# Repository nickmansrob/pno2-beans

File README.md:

# The Bean Bot

As of 20th of May 2022, this project is discontinued and will no longer be maintained.

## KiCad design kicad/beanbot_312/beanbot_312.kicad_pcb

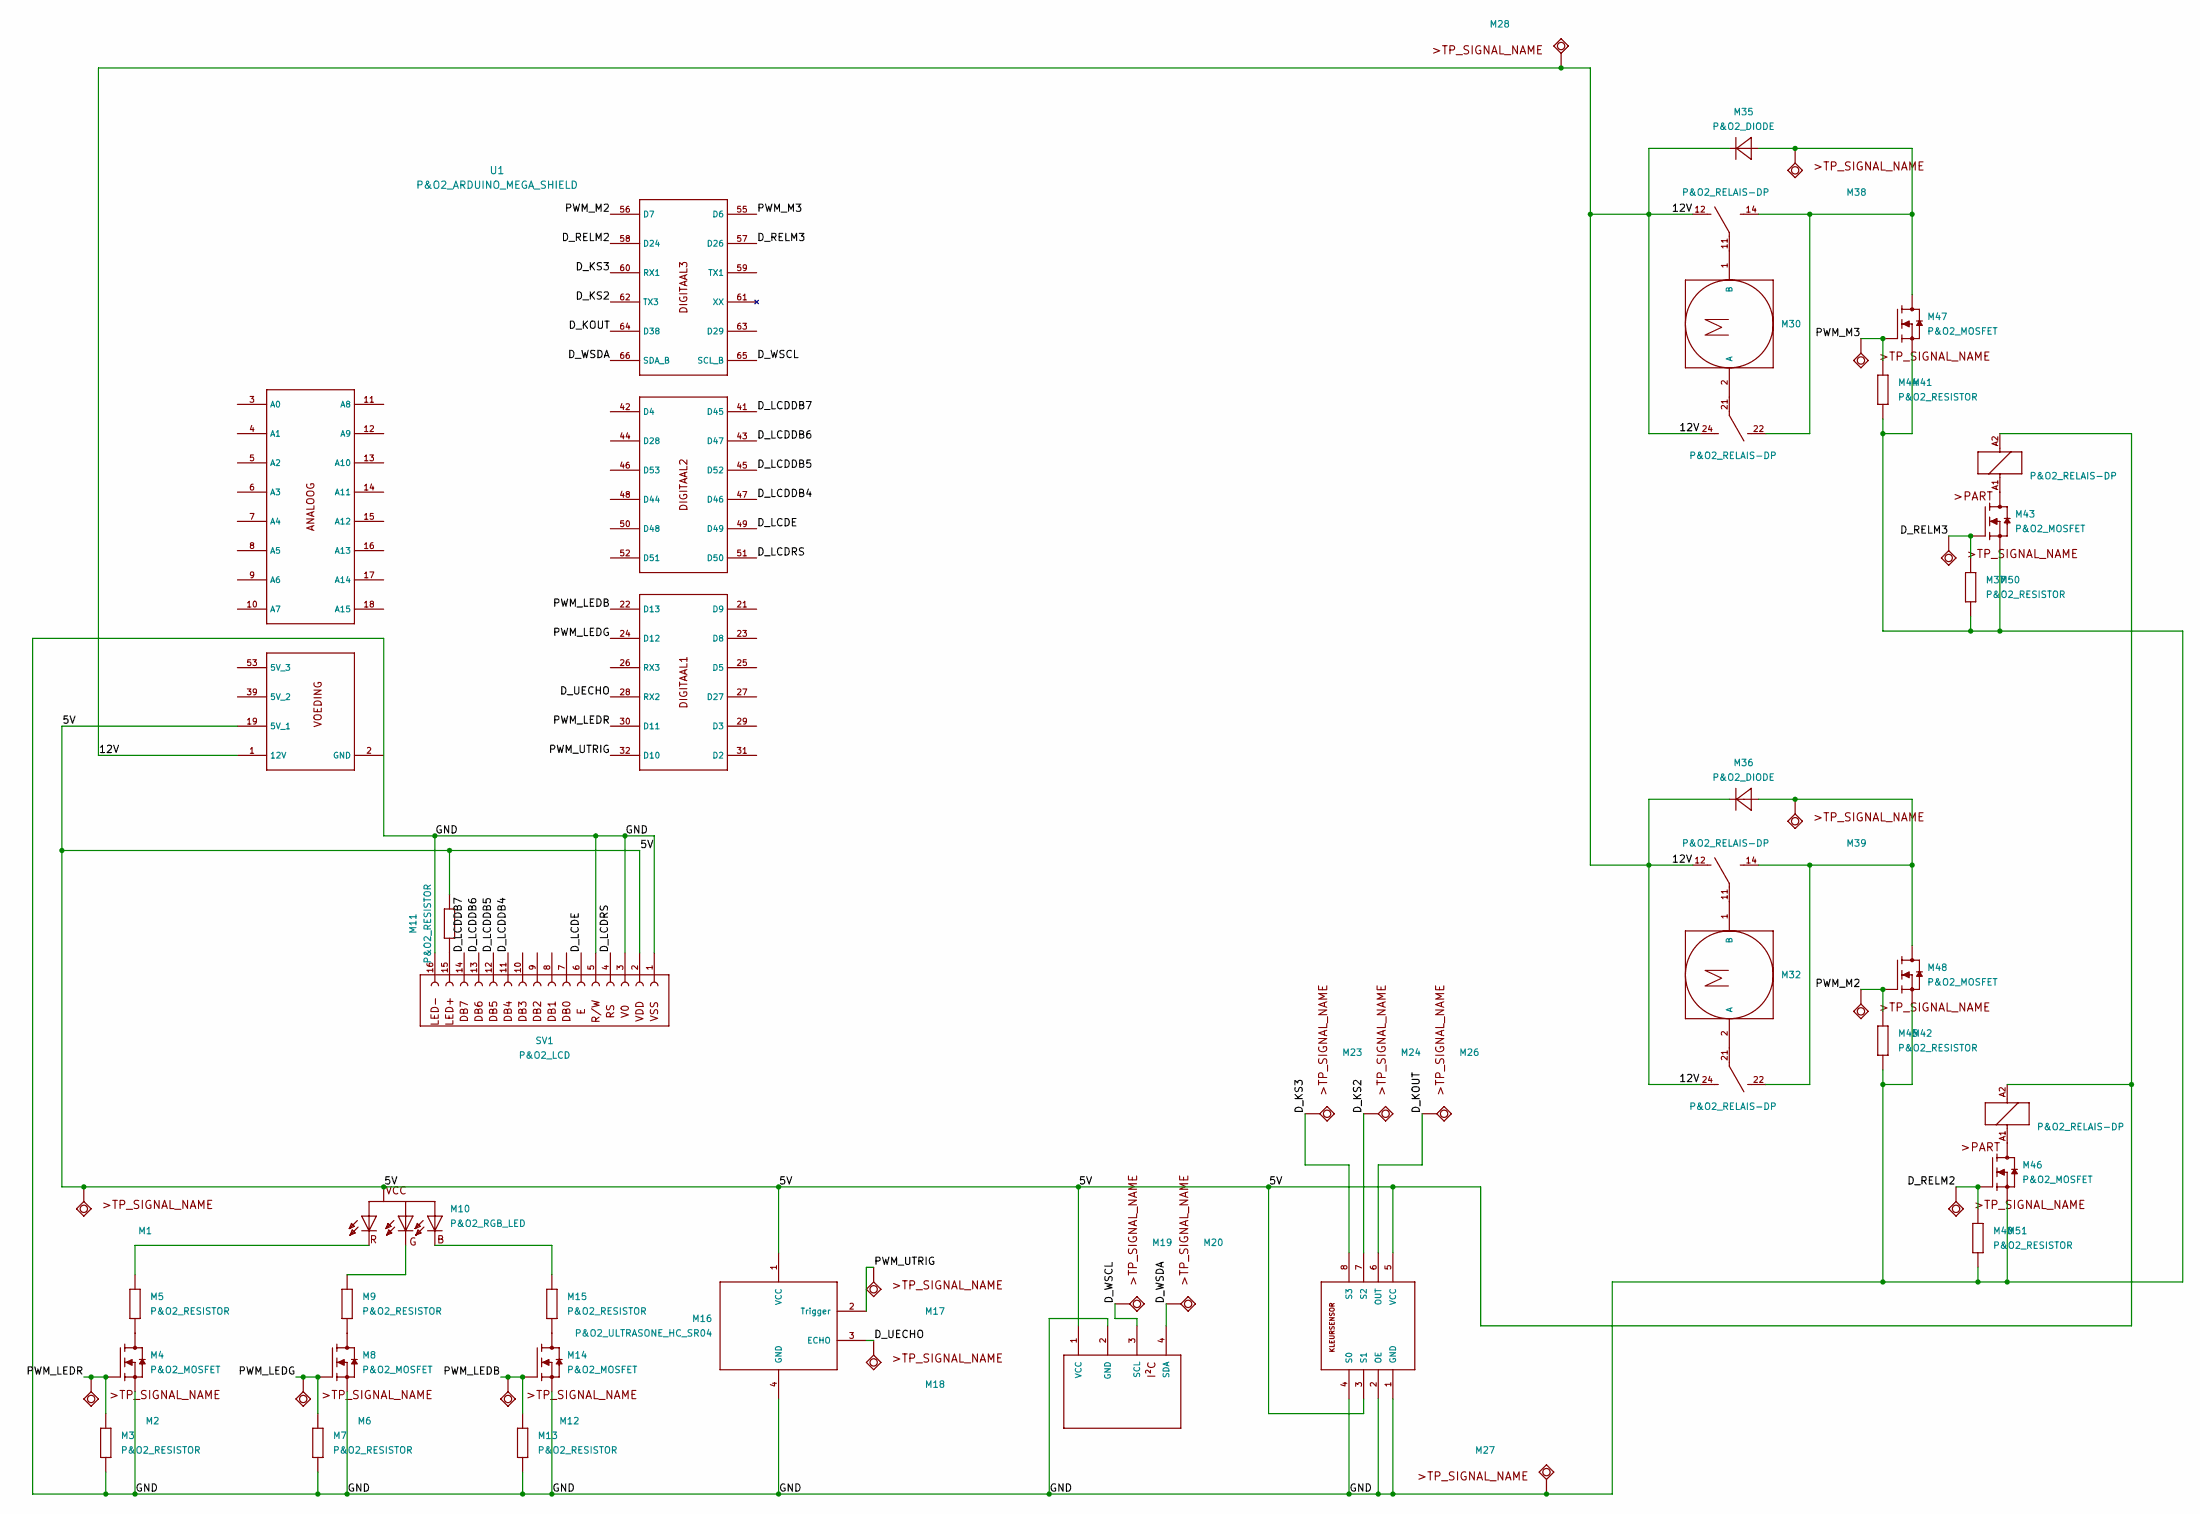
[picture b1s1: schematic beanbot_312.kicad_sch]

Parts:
M1, M2, M6, M12, M17, M18, M19, M20, M23, M24, M26, M27, M28, M38, M39, M41, M42, M50, M51: P&O2_MEETPUNT
M3, M5, M7, M9, M11, M13, M15, M37, M40, M44, M45: P&O2_RESISTOR
M4, M8, M14, M43, M46, M47, M48: P&O2_MOSFET; P&O2_TO220
M10: P&O2_RGB_LED
M16: P&O2_ULTRASONE_HC_SR04; P&O2_ULTRASONE
M21: P&O2_GEWICHTSENSOR2; P&O2_GEWICHTSENSOR-4PIN
M25: P&O2_KLEURSENSOR; P&O2_KLEURENSENSOR-8PIN
M29, M31: P&O2_RELAIS-DP; P&O2_RELAY-DP
M30, M32: P&O2_DC-MOTOR; P&O2_2PIN-SCREW-5.08
M35, M36: P&O2_DIODE
SV1: P&O2_LCD
U1: P&O2_ARDUINO_MEGA_SHIELD

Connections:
/5V: M1.1 (TP), M10.2 (VCC), M11.2, M16.1 (VCC), M21.1 (VCC), M25.3 (S1), M25.5 (VCC), M29.A2 (2), M31.A2 (2), SV1.2, U1.19 (5V_1), U1.39 (5V_2), U1.53 (5V_3)
/12V: M28.1 (TP), M29.12 (1), M29.24 (1), M31.12 (1), M31.24 (1), M35.C, M36.C, U1.1 (12V)
/D_KOUT: M25.6 (OUT), M26.1 (TP), U1.64 (D38)
/D_KS2: M24.1 (TP), M25.7 (S2), U1.62 (TX3)
/D_KS3: M23.1 (TP), M25.8 (S3), U1.60 (RX1)
/D_LCDDB4: SV1.11, U1.47 (D46)
/D_LCDDB5: SV1.12, U1.45 (D52)
/D_LCDDB6: SV1.13, U1.43 (D47)
/D_LCDDB7: SV1.14, U1.41 (D45)
/D_LCDE: SV1.6, U1.49 (D49)
/D_LCDRS: SV1.4, U1.51 (D50)
/D_RELM2: M40.1, M46.1 (eG), M51.1 (TP), U1.58 (D24)
/D_RELM3: M37.1, M43.1 (eG), M50.1 (TP), U1.57 (D26)
/D_UECHO: M16.3 (ECHO), M18.1 (TP), U1.28 (RX2)
/D_WSCL: M19.1 (TP), M21.3 (SCL), U1.65 (SCL_B)
/D_WSDA: M20.1 (TP), M21.4 (SDA), U1.66 (SDA_B)
/GND: M3.2, M4.3 (S), M7.2, M8.3 (S), M13.2, M14.3 (S), M16.4 (GND), M21.2 (GND), M25.1 (GND), M25.2 (OE), M25.4 (S0), M27.1 (TP), M37.2, M40.2, M43.3 (S), M44.2, M45.2, M46.3 (S), M47.3 (S), M48.3 (S), SV1.1, SV1.3, SV1.5, SV1.16, U1.2 (GND)
/PWM_LEDB: M12.1 (TP), M13.1, M14.1 (eG), U1.22 (D13)
/PWM_LEDG: M6.1 (TP), M7.1, M8.1 (eG), U1.24 (D12)
/PWM_LEDR: M2.1 (TP), M3.1, M4.1 (eG), U1.30 (D11)
/PWM_M2: M42.1 (TP), M45.1, M48.1 (eG), U1.56 (D7)
/PWM_M3: M41.1 (TP), M44.1, M47.1 (eG), U1.55 (D6)
/PWM_UTRIG: M16.2 (Trigger), M17.1 (TP), U1.32 (D10)
unnamed: M4.2 (D), M5.2
unnamed: M8.2 (D), M9.2
unnamed: M5.1, M10.1 (R)
unnamed: M9.1, M10.3 (G)
unnamed: M10.4 (B), M15.1
unnamed: M11.1, SV1.15
unnamed: M14.2 (D), M15.2
unnamed: M29.11 (1), M30.1 (B)
unnamed: M29.14 (1), M29.22 (1), M35.A, M38.1 (TP), M47.2 (D)
unnamed: M29.21 (1), M30.2 (A)
unnamed: M29.A1 (1), M43.2 (D)
unnamed: M31.11 (1), M32.1 (B)
unnamed: M31.14 (1), M31.22 (1), M36.A, M39.1 (TP), M48.2 (D)
unnamed: M31.21 (1), M32.2 (A)
unnamed: M31.A1 (1), M46.2 (D)

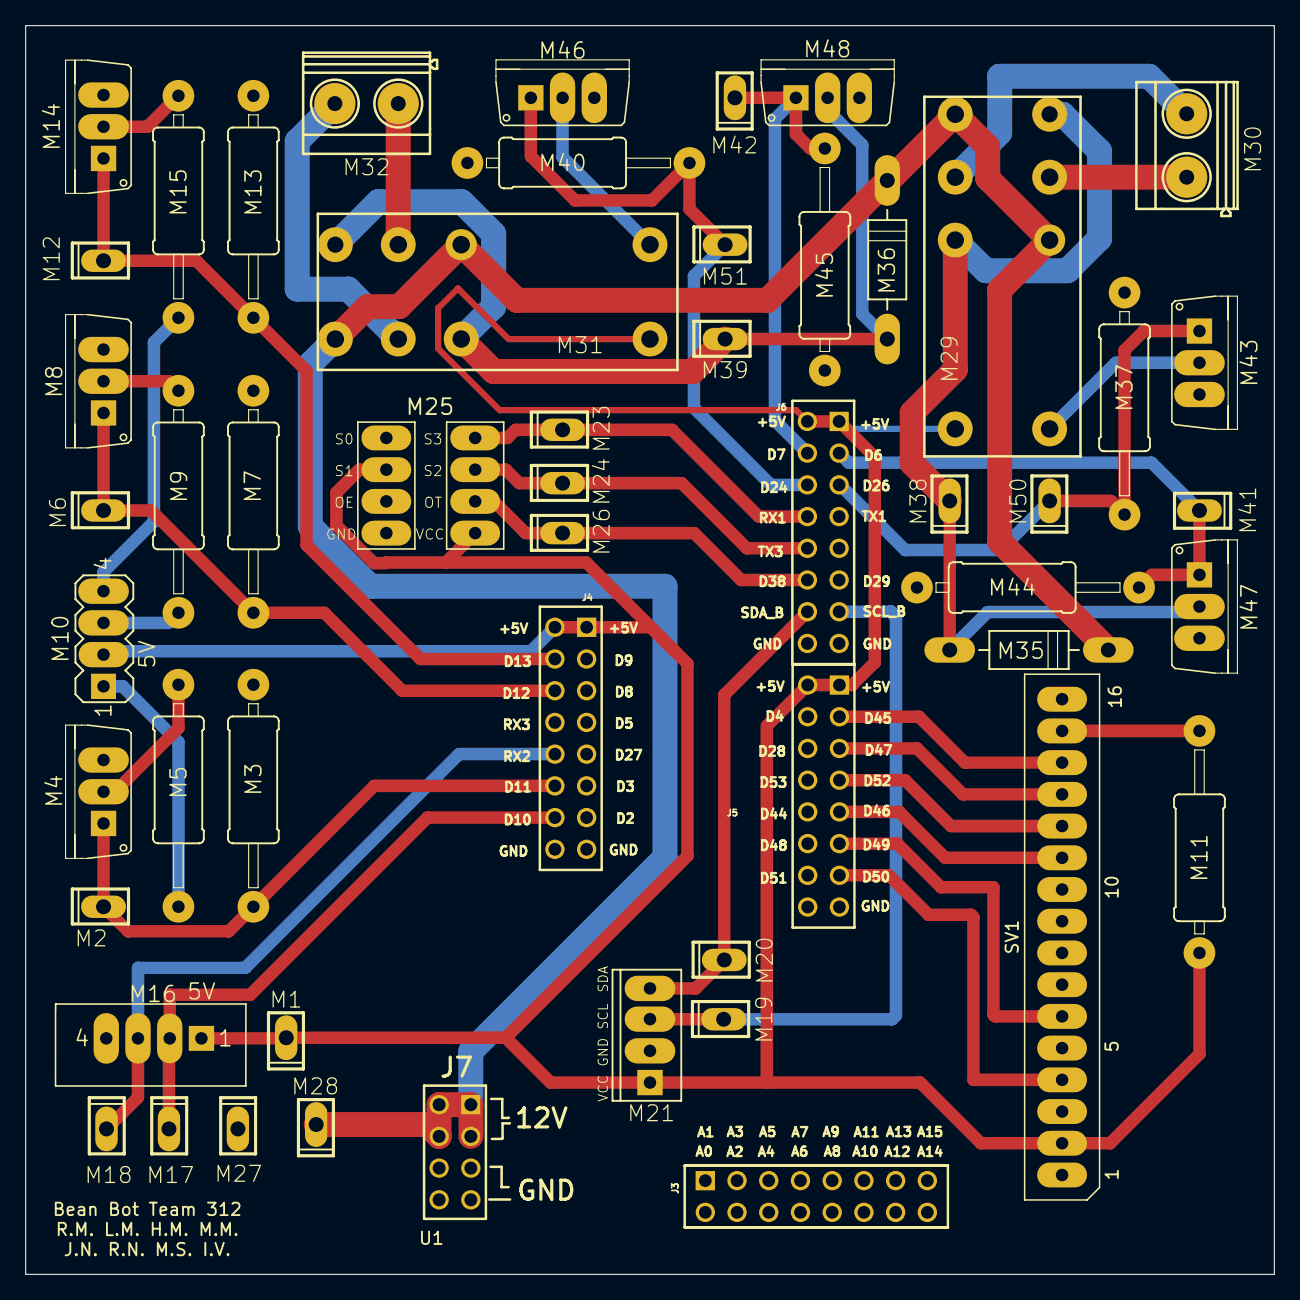
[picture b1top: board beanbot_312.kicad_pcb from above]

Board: 2 copper layers, 100.0 x 100.0 mm, 49 parts (0 on the bottom side), 38 nets.

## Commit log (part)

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2022-02-18 Initialized Flutter
2022-02-26 Created initial UI
2022-02-26 added arduino code
2022-02-26 moved readme
2022-02-26 Added navigation with PopupMenu
2022-02-27 Progress to logs page
2022-02-27 Some Progress on Debug Menu
    I created a Debug page like you created in the PDF document. It was not yet possible to properly implement the output containers due to problems with the heigth.
2022-02-27 Grouped items in debug.dart
2022-02-27 Force fix
2022-02-27 Update README (#1)
2022-03-03 Add ShowWeigth
2022-03-03 Added manual override
2022-03-03 established connection
2022-03-03 finished publishing
2022-03-03 added change ip button
2022-03-04 Commit changes
2022-03-04 added mqtt connection
2022-03-05 implemented handlers
2022-03-05 cleanup
2022-03-06 fixed pointer issue
2022-03-06 added kicad drawings
2022-03-06 added arduino compat
2022-03-06 Added Ip button
2022-03-07 Arduino/add mqtt (#5)
    * established connection
    * finished publishing
    * added change ip button
    * added mqtt connection
    * implemented handlers
    * cleanup
2022-03-08 Progress on KiCad drawings
2022-03-08 Some progress on the home page
2022-03-08 Minor improvements to the structure of the homepage
2022-03-08 Added IP validation
    I wrote a function to validate an entered IP address. I should work with any valid IPv4 address.
2022-03-08 Hidden IP input behind foldable widget
2022-03-08 Some Progress to KiCad drawings
2022-03-08 Make bean order work
2022-03-08 Add currentWeight and currentOrder on homepage
2022-03-09 Deleting wires and adding labels
2022-03-09 Some Progress to KiCad drawings (#8)
    * Some Progress to KiCad drawings
    * Some more progress to KiCad drawings
    * Deleting wires and adding labels
2022-03-09 Added subscription to multiple topics
2022-03-09 Finished kicad
2022-03-09 Revert "Merge branch 'master' into addip"
    This reverts commit 289b15b6f1f409cac43bb7c3f2ab455e36746644.
2022-03-09 Added resistors
2022-03-09 Updated footprints and balance
2022-03-09 Finished schematic
2022-03-09 Schematics (#9)
    * Some Progress to KiCad drawings
    * Some more progress to KiCad drawings
    * Deleting wires and adding labels
    * Finished kicad
    * Added resistors
    * Added labels and modified LCD
2022-03-09 Fixed code format
2022-03-09 Fix merge conflict
2022-03-09 Add IP input method and make connectionState available throughout the app (#6)
    * Added Ip button
    * Made connectionState available throughout the app
    * Some progress on the home page
    * Minor improvements to the structure of the homepage
    * Added IP validation
    I wrote a function to validate an entered IP address. I should work with any valid IPv4 address.
2022-03-10 Made the LogPage
    When the Arduino sends data over the 'logListener' topic, it will be displayed on the LogPage of the app. I also added a button to clear out the logs in the app.
2022-03-10 Added IC to KiCad
2022-03-10 Latest changes
2022-03-10 Fixed scheme
2022-03-11 Changed DC to servomotor
2022-03-12 Grey out buttons when disconnected
2022-03-12 Grey out log button when disconnected
2022-03-12 Refactored schematic
2022-03-12 Grey out buttons when disconnected (#14)
    * Grey out buttons when disconnected
    * Grey out log button when disconnected
2022-03-12 Show connection error when not connecting to broker
2022-03-12 Add KiCad changes (#13)
    * Added IC to KiCad
    * Latest changes
    * Fixed scheme
    * Changed DC to servomotor
    * Latest changes
    * Refactored schematic
2022-03-12 Recovery
2022-03-12 Added additional motors
2022-03-13 Fixed grey screen issue
    I fixed the issue that the buttons went grey when they were disabled. Furthermore, I changed the button layout and removed the redundant buttons. For controlling the Arduino, there is now one reset b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
2022-03-13 Fixed grey out issue on home page
2022-03-13 Fixed error
2022-03-13 Show connection error when not connecting to broker (#19)
    * Show connection error when not connecting to broker
    * Fixed grey out issue on home page
2022-03-13 Add greyed out for manualOverride (#18)
    * Add greyed out for manualOverride
    * Fixed grey screen issue
    I fixed the issue that the buttons went grey when they were disabled. Furthermore, I changed the button layout and removed the redundant buttons. For controlling the Arduino, there is now one reset b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
2022-03-13 Fix weigth input bug
2022-03-13 Changed icon
2022-03-13 Make cancel button work
2022-03-13 Fix weigth input bug (#22)
    * Fix weigth input bug
    * Make cancel button work
2022-03-13 Changed icon (#23)
2022-03-13 Add progress bar for weight.
2022-03-16 Order changes
2022-03-16 Make debugpage work
2022-03-16 Solve progressbar overflow
2022-03-16 Added labels and measuring point
2022-03-17 Make colorlistener work and show message on end order
    This commits makes the color determining feature work and shows a message when the order is finished. Then the order is deleted from the home screen.
2022-03-18 Latest KiCad changes
2022-03-18 Restore latest version
2022-03-18 added pinnumbers and extended code in general
2022-03-19 Add override and change rotation
    When the manual override switch is turned on, the app sends 'restore' on the order topic.
    I also added a change rotation button for every DC-motor, as well as a small validation for the servos.
2022-03-19 Add underscore in change_rotation
2022-03-19 Change package send by manual override
2022-03-19 Add override and change rotation (#26)
    * Add override and change rotation
    When the manual override switch is turned on, the app sends 'restore' on the order topic.
    I also added a change rotation button for every DC-motor, as well as a small validation for the servos.
    * Add underscore in change_rotation
    * Change package send by manual override
2022-03-19 Add weight sensor and LCD display
2022-03-19 Add sensor input for color sensor and ultrasonic sensor.
2022-03-19 Added sensor input
2022-03-19 Made outline for pcb
2022-03-19 Moved all components for an overview
2022-03-19 First attempt for DC motor & tweaked scheme a little
2022-03-19 Almost finished
2022-03-20 Fix warnings
2022-03-20 Add forgotten file
2022-03-20 Deleted hidden 5V label
2022-03-20 Fix bugs in app
    I made it impossible for the user to add more than 2 orders at the same time. The order remain on the screen until the Arduino sends 'done_all' via adminListener.
2022-03-20 Second order send on done first
2022-03-21 Change done to pt
2022-03-22 Add change_rotation implementation
2022-03-22 Add small changes
2022-03-22 Change rotate function
2022-03-22 Make compile changes
2022-03-22 Arduino code (#20)
    * Recovery
    * Added additional motors
    * added pinnumbers and extended code in general
    * Added sensor input
    * Made requested changes
    * Made requested changes
2022-03-22 Arduino fix (#30)
2022-03-22 First progres on changes
2022-03-22 Changed normal flow
2022-03-22 Add semicolon
2022-03-22 Implement adminListener
2022-03-22 Deleted abort boolean
2022-03-22 Implement normal flow (#31)
    * Changed normal flow
    * Add semicolon
    * Deleted abort boolean
2022-03-22 Append to normal flow
2022-03-23 Fix second order push
2022-03-23 Added footprints
2022-03-24 First progress on Arduino and Nodemcu
2022-03-24 fsdf
2022-03-24 assd
2022-03-24 blabl
2022-03-24 Updated pcb
2022-03-24 Some progress on the PCB
2022-03-24 Change border
2022-03-24 Finished PCB
2022-03-24 Changed team name location
2022-03-24 Properly send from Arduino to MCU
2022-03-24 Final changes to PCB
2022-03-25 Manualoverride sends 0 and 1
2022-03-25 Files changes for Arduino
2022-03-25 Add Arduino wifi shield code
2022-03-25 Arduino/addserial (#35)
    * Append to normal flow
    * First progress on Arduino and Nodemcu
    * fsdf
    * assd
    * Latets update
    * Properly send from Arduino to MCU
2022-03-25 Cleared warnings
2022-03-25 Make manualoverride work
2022-03-25 Make manualoverride work (#36)
2022-03-25 PCB (#28)
    * Made outline for pcb
    * Moved all components for an overview
    * First attempt for DC motor & tweaked scheme a little
    * Almost finished
    * Fix warnings
    * Add forgotten file
2022-03-25 Restored code
2022-03-26 App Fix issues
2022-03-27 App Fix issues (#40)
2022-03-27 Updated version
2022-03-28 Some progress on sensors
2022-03-28 Add sensors in app
2022-03-28 Added code
2022-03-28 Latests progress
2022-03-29 Arduino add sensors in app
2022-03-29 Implement sensors in app (#41)
    * Add sensors in app
    * Add sensors in app
    * Fix connection bugs
    * Latest changes
2022-03-29 Cleanup and states
2022-03-29 Added all states
2022-03-29 Work
2022-03-29 CODE FOR DEMO
2022-03-29 LATEST APP CHANGES
2022-03-30 Make arduino compatible with app
2022-03-30 Fix bugs in code
2022-03-30 Esthetics
2022-03-30 Added relay mosfets and ground connections
2022-03-30 Backups
2022-04-01 Gerbers
2022-04-05 Add technical drawings to GitHub
    History showed that some version control is nice.
2022-04-06 Move technical drawings to assets
2022-04-11 Added looping over all RGB-values
2022-04-12 Making colorcalibration work in app
2022-04-12 Add navigation menus on all pages
    Don't judge the sketchy implementation, it works :).
2022-04-14 Add python script to read SerialMonitor
    Feedback is more than welcome.
2022-04-14 New method for calibrating color sensor via MQTT
2022-04-14 Arduino Code for color calibration
2022-04-14 Make python script compatible with calibration function changes
2022-04-19 Solve #50 (#51)
    * Some progress on color calibration in app
    * Added looping over all RGB-values
    * Making colorcalibration work in app
    * Add navigation menus on all pages
    Don't judge the sketchy implementation, it works :).
    * Add python script to read SerialMonitor
2022-04-19 Workflow
2022-04-19 Delete
2022-04-19 dart format
2022-04-19 dart format (#53)
2022-04-19 Fix weightcursor issue
2022-04-19 Fix weightcursor issue (#55)
2022-04-19 Revert "Workflow"
    This reverts commit 8b8b0cdb2aaa86cb095527eeb7ff8a93aec453df.
2022-04-20 First round of app refactor
2022-04-21 Second round of app refactor
2022-04-21 Final round of app refactor
2022-04-21 Added weight
2022-04-21 Changes node
2022-04-21 Changes from 21/04
2022-04-22 Refactor of the Arduino Mega, WIP
2022-04-23 Making the color calibration work.
2022-04-23 First try with color calibration
2022-04-23 Veni, vidi, reverti.
2022-04-26 Fix faulty function
2022-04-26 ArduinoMega refactor
2022-04-26 NodeMCU refactor
2022-04-27 libs
2022-04-27 voltage
2022-04-28 Add MATLAB fit to project
2022-04-28 Code could possibly by corrupt
2022-04-28 Code is only half corrupt.
2022-04-28 Fixed bugs in `weightDone`
2022-04-28 Fixed further bugs in ordering beans
2022-04-29 Edited kicad scheme and pcb
2022-04-30 Fix bugs in app
2022-05-04 Added RGB control function in Arduino Mega
2022-05-04 Pin changes
2022-05-04 RGB control in the NodeMCU
2022-05-04 Remove corrupt code
2022-05-05 Add RGB control in app
2022-05-05 Fix dumb mistake
2022-05-07 Added version control to 'verslag'
2022-05-08 Changed code for servos
2022-05-10 Servo implement
2022-05-10 Added flowchart MCU
2022-05-10 Servo Three
2022-05-10 Normalflow
2022-05-10 App changes...
2022-05-11 Final app changes
2022-05-11 Auto stash before rebase of "origin/master"
2022-05-11 Initialize
2022-05-11 normalFlow in mcu
2022-05-12 normalFlow()
2022-05-13 Updated flow
2022-05-13 NormalRobin
2022-05-13 Finished flow
2022-05-13 Added in loop
2022-05-13 manualflow
2022-05-15 Ugly fix, but kinda works.
2022-05-15 Flowchart updates and added belt emptier
2022-05-15 Added arduino drawio
2022-05-16 Important patch
2022-05-16 Patch 2
2022-05-16 Constantes invullen
2022-05-16 Flowcharts
2022-05-16 Flowcharts and app abort for arduino
2022-05-16 Changes to interrupt
2022-05-16 Flowchart changes
2022-05-17 Add right flowchart
2022-05-17 Change extension
2022-05-17 Organize and plot
2022-05-17 Interrupt
2022-05-17 Improvements
2022-05-17 Flowchart
2022-05-18 Final commit
